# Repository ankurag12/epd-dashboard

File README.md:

# stoic-dashboard

**Dashboard that displays a new Stoic thought everyday!**

The main components of the project are:

- [Plastic Logic's Electrophoretic Display (EPD)](https://www.plasticlogic.com/product/parrot-msp430-for-10-7-display/):
  Similar to an E-ink display; it's optimal for this application as it consumes energy only when the image is updated.
- [Adafruit HUZZAH32-ESP32](https://learn.adafruit.com/adafruit-huzzah32-esp32-feather): An ESP32 board. This runs the
  firmware for the dashboard in MicroPython, and provides functionality like connecting to a WiFi network, pulling image
  from the server, and sending it to the EPD controller.
- [ESP32-EPD Adapter](designs): The original eval-kit from Plastic Logic is powered by an MSP430 MCU. However, I wanted
  to run it using an ESP32 for features like WiFi connectivity and Python compatibility. So I made this adapter board
  that stacks on top of the Adafruit HUZZAH32-ESP32 and connects to the FPC that goes to the EPD controller board (Raven), replacing the MSP430 board (Parrot).
- [RaspberryPi](https://www.raspberrypi.com/products/raspberry-pi-4-model-b/): It acts as a server that runs 24x7,
  maintaining a repository of images by pulling from Instagram
  account [@dailystoic](https://www.instagram.com/dailystoic/) and serving it to ESP32.

Other accessories include

- 3.7V LiPo battery
- [FFC/FPC extenders](https://www.adafruit.com/search?q=0.5mm+FFC+%2F+FPC+Extender) + [Flex cables](https://www.amazon.com/dp/B00W8W9PZO)
  to make connecting different boards easier after framing
- Frame using [foam-board](https://www.michaels.com/product/20-x-30-white-foam-board-10110205)
  and [leather sheet](https://www.amazon.com/gp/product/B08XJW7ZDR) (because I didn't have access to woodworking tools!)

This repo contains the ESP32 firmware ([frontend](frontend)), RPi server code ([backend](backend)) and design files for
the ESP32-EPD adapter ([designs](designs)).

## backend

Run this code on a permanently powered and internet connected system like a RaspberryPi. If a RaspberryPi isn't
available, any computer running Python can be used as a server. Just make sure to update the URL
in [main.py](frontend/main.py).

To setup, create a Python venv and install dependencies

```commandline
cd backend
python -m venv .env
source ./.env/bin/activate
pip install -U pip
pip install -r requirements.txt
```

and run the server indefinitely.

```commandline
nohup python server.py &
```

After a few seconds, there should be images downloaded in `backend/image_repo`. You can verify that the server is
working well by visiting http://raspberrypi.local:8080 in your browser.

The server maintains a queue of available images from `image_repo`, popping one out whenever client (ESP32) queries. If
the size of the queue drops below a threshold (default=10), it executes another pull from Instagram to
update `image_repo` and the queue.

To avoid repeating images, it also maintains a history of previously served images as `history.pkl`. Delete that file to
recycle old images.

## frontend

This is a MicroPython port of the
original [MSP430 firmware from PlasticLogic](https://github.com/plasticlogic/pl-mcu-epd) (written in C) with some modifications like
pulling the image to display from a server on the network instead of reading from an SD-card.

If not done already, follow the steps here to
prepare [ESP32 for MicroPython](https://docs.micropython.org/en/latest/esp32/tutorial/intro.html).

Create a Python3.7 venv and install dependencies

```commandline
cd frontend
python3.7 -m venv .env
source ./.env/bin/activate
pip install -U pip
pip install -r requirements.txt
```

Change WiFi and SSID and password in [wifi.json](frontend/wifi.json), and run `run.sh`

```commandline
./run.sh
```

This will transfer all frontend code and configs to the ESP32, pull an image from the server, display it on the EPD, and
go to [deep sleep](https://lastminuteengineers.com/esp32-deep-sleep-wakeup-sources/) for approx 24 hours. On wake-up, it
will pull and display a new image.

Before running `run.sh`, make sure that the server is running, else the frontend code will crash because
it can't find server! If that happens, perform a hard reset

```commandline
ampy --port /dev/cu.SLAB_USBtoUART reset --hard
```

#### Changing an image on demand

If you want to change the current image (and understandably don't want to wait 24 hours), ESP32 has a way to wake-up
from deep sleep
using [touch](https://docs.micropython.org/en/latest/esp32/quickref.html?highlight=deep_sleep#capacitive-touch). ESP32
has several capacitive touch-enabled pins; I'm using GPIO #14 that I fly-wired to a corner of the dashboard. Touching
that corner wakes up the ESP32 and updates the image. It could take ~20s, but still pretty cool! 

## designs
I used KiCad for designing the adapter board.

## Why Stoic?
Because I find it interesting 🤷

But yeah, technically, it's a generic dashboard, and one can add any number of Instagram accounts as `SOURCES` in [server.py](backend/server.py) :)

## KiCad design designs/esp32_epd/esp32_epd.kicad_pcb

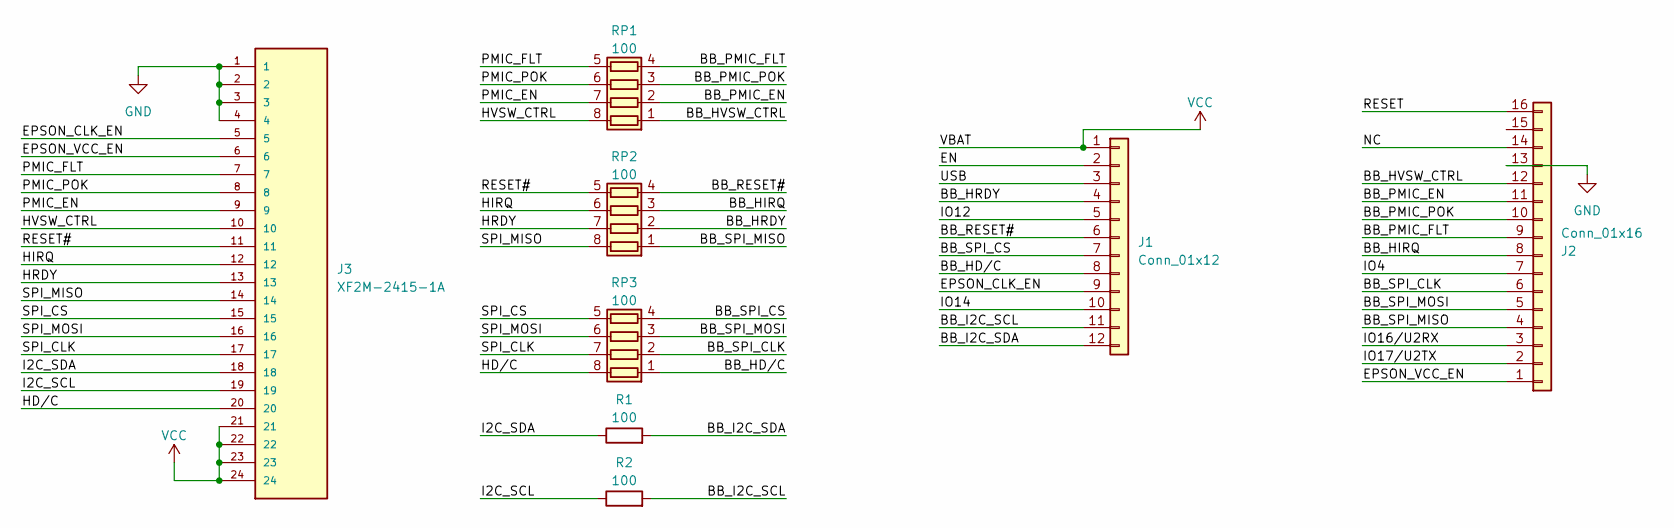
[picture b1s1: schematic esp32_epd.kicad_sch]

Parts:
J1: Conn_01x12; PinHeader_1x12_P2.54mm_Vertical
J2: Conn_01x16; PinHeader_1x16_P2.54mm_Vertical
J3: XF2M-2415-1A; OMRON_XF2M-2415-1A
R1, R2: 100; R_0603_1608Metric_Pad0.98x0.95mm_HandSolder
RP1, RP2, RP3: 100; RESCAXE80P320X160X70-8N

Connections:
/BB_HD/C: J1.8, RP3.1 (R1.1)
/BB_HIRQ: J2.8, RP2.3 (R3.1)
/BB_HRDY: J1.4, RP2.2 (R2.1)
/BB_HVSW_CTRL: J2.12, RP1.1 (R1.1)
/BB_I2C_SCL: J1.11, R2.2
/BB_I2C_SDA: J1.12, R1.2
/BB_PMIC_EN: J2.11, RP1.2 (R2.1)
/BB_PMIC_FLT: J2.9, RP1.4 (R4.1)
/BB_PMIC_POK: J2.10, RP1.3 (R3.1)
/BB_RESET#: J1.6, RP2.4 (R4.1)
/BB_SPI_CLK: J2.6, RP3.2 (R2.1)
/BB_SPI_CS: J1.7, RP3.4 (R4.1)
/BB_SPI_MISO: J2.4, RP2.1 (R1.1)
/BB_SPI_MOSI: J2.5, RP3.3 (R3.1)
/EN: J1.2
/EPSON_CLK_EN: J1.9, J3.5
/EPSON_VCC_EN: J2.1, J3.6
/HD/C: J3.20, RP3.8 (R1.2)
/HIRQ: J3.12, RP2.6 (R3.2)
/HRDY: J3.13, RP2.7 (R2.2)
/HVSW_CTRL: J3.10, RP1.8 (R1.2)
/I2C_SCL: J3.19, R2.1
/I2C_SDA: J3.18, R1.1
/IO4: J2.7
/IO12: J1.5
/IO14: J1.10
/IO16/U2RX: J2.3
/IO17/U2TX: J2.2
/NC: J2.14
/PMIC_EN: J3.9, RP1.7 (R2.2)
/PMIC_FLT: J3.7, RP1.5 (R4.2)
/PMIC_POK: J3.8, RP1.6 (R3.2)
/RESET: J2.16
/RESET#: J3.11, RP2.5 (R4.2)
/SPI_CLK: J3.17, RP3.7 (R2.2)
/SPI_CS: J3.15, RP3.5 (R4.2)
/SPI_MISO: J3.14, RP2.8 (R1.2)
/SPI_MOSI: J3.16, RP3.6 (R3.2)
/USB: J1.3
GND: J2.13, J3.1, J3.2, J3.3, J3.4
VCC: J1.1, J3.21, J3.22, J3.23, J3.24

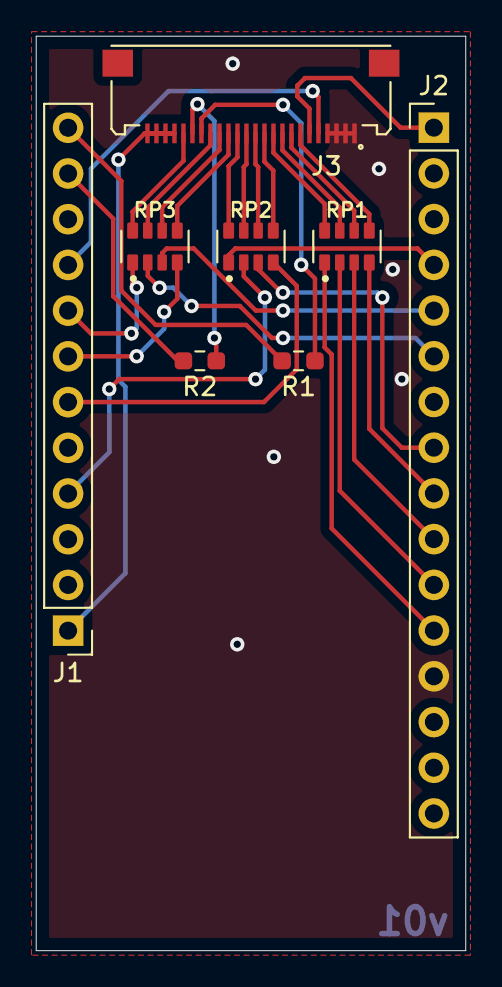
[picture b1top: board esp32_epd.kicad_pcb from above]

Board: 2 copper layers, 23.9 x 50.8 mm, 8 parts (0 on the bottom side), 32 nets.

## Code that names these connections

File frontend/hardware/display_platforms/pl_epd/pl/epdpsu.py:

class EPDPSU:
    def __init__(self):
        self._state = 0

    def on(self):
        raise NotImplementedError

    def off(self):
        raise NotImplementedError


class EpdPsuGPIO(EPDPSU):
    def __init__(self, mcu, timeout_ms=300, on_delay_ms=5, off_delay_ms=100):
        super().__init__()
        self._mcu = mcu
        self._timeout_ms = timeout_ms
        self._on_delay_ms = on_delay_ms
        self._off_delay_ms = off_delay_ms

    def on(self):
        if self._state == 1:
            return

        self._mcu["GPIO"]["PMIC_EN"].set_pin(1)

        start = self._mcu.ticks_ms()

        while self._mcu["GPIO"]["PMIC_POK"].get_pin() != 1:
            if self._mcu.ticks_diff(self._mcu.ticks_ms(), start) > self._timeout_ms:
                self._mcu["GPIO"]["PMIC_EN"].set_pin(0)
                raise TimeoutError(f"Timeout waiting for PMIC_OK")
            self._mcu.sleep_ms(1)

        self._mcu["GPIO"]["HVSW_CTRL"].set_pin(1)
        self._mcu.sleep_ms(self._on_delay_ms)

        self._state = 1

    def off(self):
        self._mcu["GPIO"]["HVSW_CTRL"].set_pin(0)
        self._mcu["GPIO"]["PMIC_EN"].set_pin(0)
        self._mcu.sleep_ms(self._off_delay_ms)
        self._state = 0


class EpdPsuEPDC(EPDPSU):
    def __init__(self, epdc):
        super().__init__()
        self._epdc = epdc

    def on(self):
        if not self._state:
            self._epdc.set_epd_power(1)
            self._state = 1

    def off(self):
        if self._state:
            self._epdc.set_epd_power(0)
            self._state = 0

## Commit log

2023-01-03 Add micropython blinky for esp32
2023-01-03 Add pl-mcu-epd as submodule
2023-01-03 Update pl-mcu-epd to work with slideshow
2023-01-16 Packet-like data comm b/w MSP430 and ESP32
2023-01-22 Init Skeleton
2023-01-29 Implement SPI
2023-02-27 Implement EPD and everything
2023-03-06 Fix runtime bugs, clear display successfully
2023-03-07 Display (small) image
2023-03-27 Transfer file over HTTP
2023-03-27 Add backend for downloading images from Instagram (WIP)
2023-03-27 Add PCB schematic and layout for ESP32-EPD adapter
2023-04-02 Backend image server and image repo builder from instagram
2023-04-10 Lightsleep after display, wakeup on touch
2023-04-10 Use deep sleep
2023-04-10 Rotate image by 90 deg
2023-05-06 Change server to RPi, Add GPIO config for HRDY to keep it low
2023-05-17 Backend: Fix bug in tracking history
2023-05-17 Clear screen on hard reset, log in txt file
2023-05-28 Add timestamps in logs, selected lines to txt, update README
2023-05-28 Fix PCB sch and layout with VCC->VBAT
2023-05-28 Add dashboard pics
2026-04-05 Use mpremote instead of ampy
